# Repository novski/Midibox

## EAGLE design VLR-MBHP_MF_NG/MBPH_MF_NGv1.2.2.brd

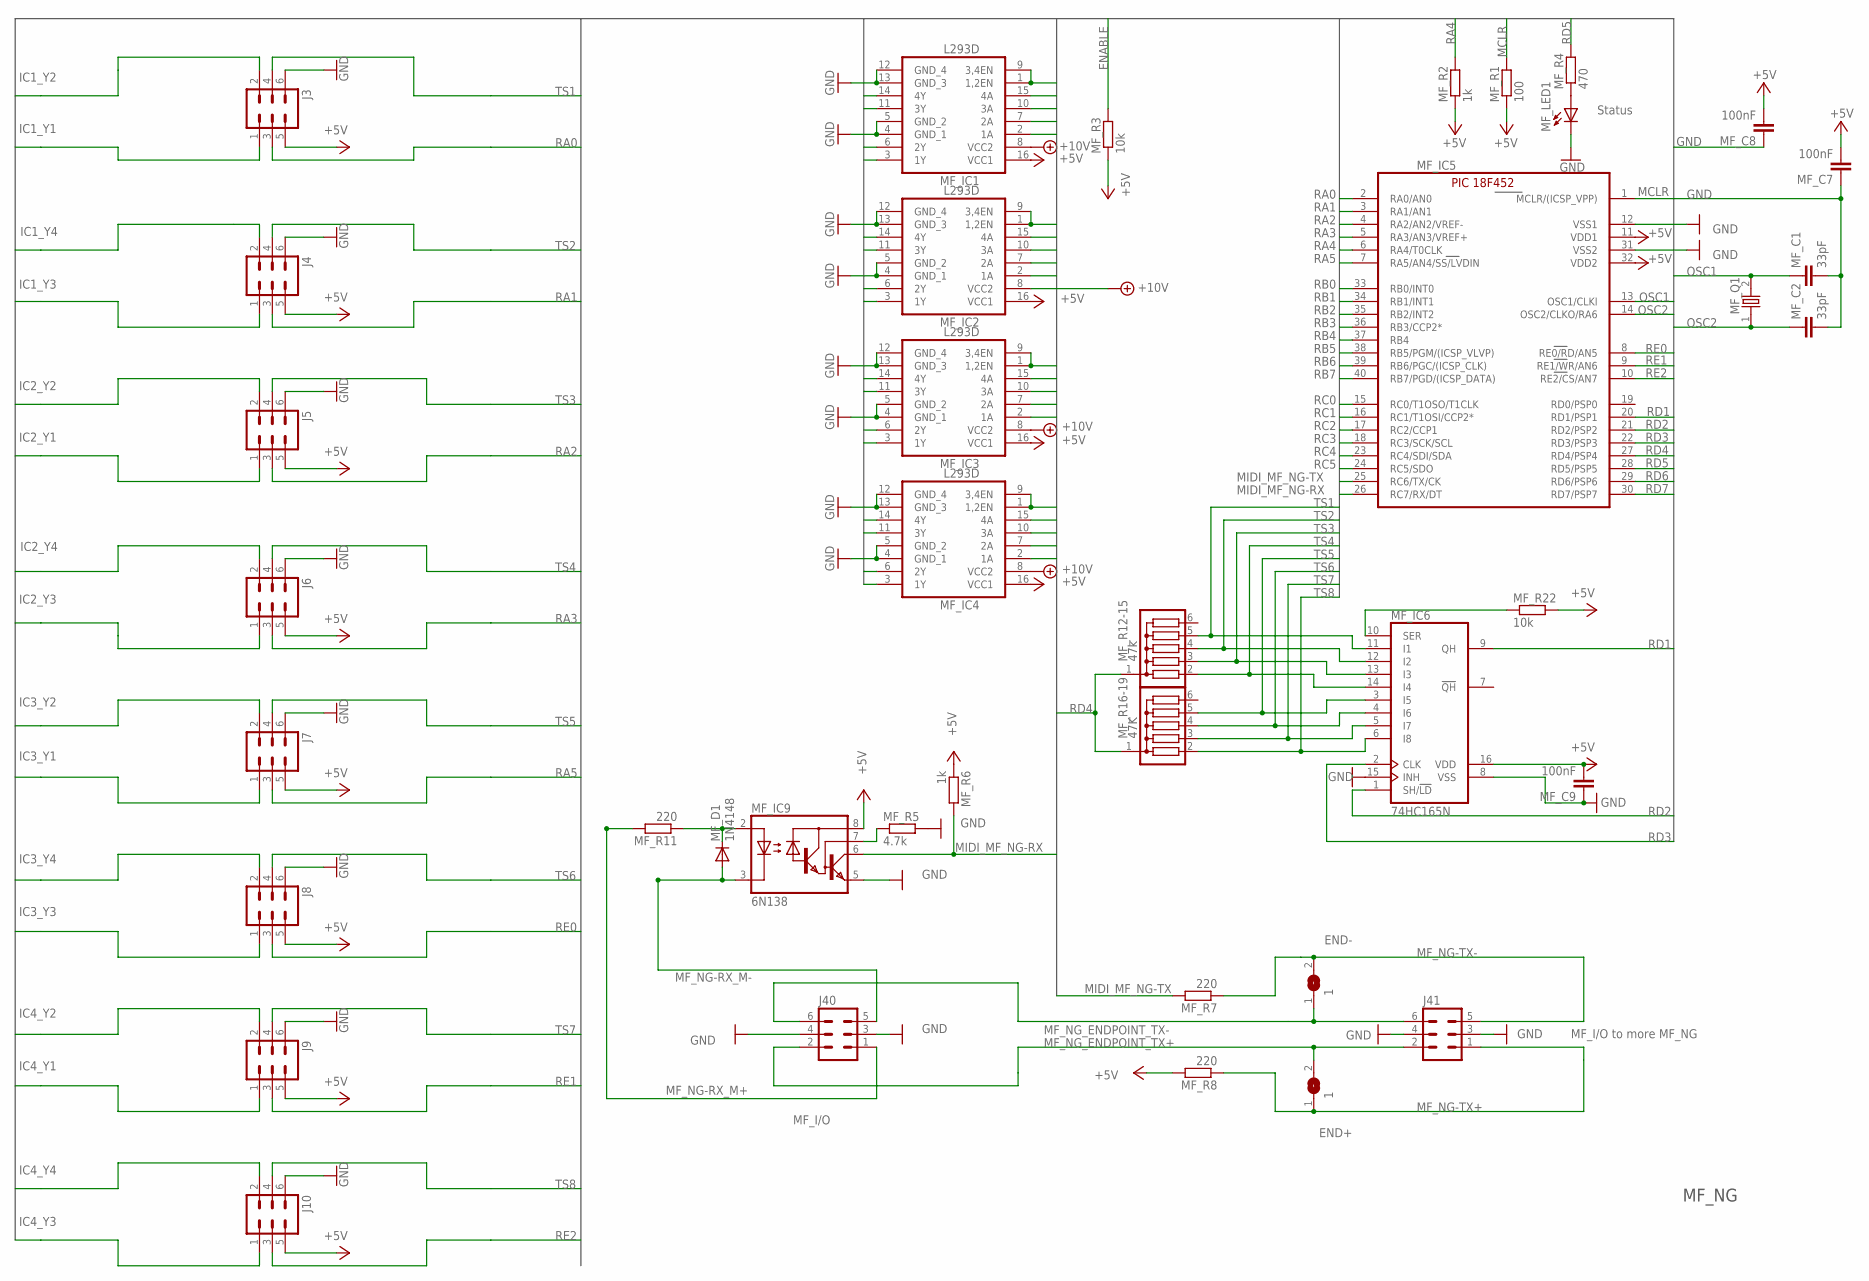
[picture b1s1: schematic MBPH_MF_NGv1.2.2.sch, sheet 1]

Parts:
END+: 1; SJ
END-: 1; SJ
J3, J4, J5, J6, J7, J8, J9, J10: ML6
J40: MF_I/O; ML6
J41: MF_I/O to more MF_NG; ML6
MF_C1, MF_C2: 33pF; C025-030X050
MF_C7, MF_C8, MF_C9: 100nF; C5B3
MF_D1: 1N4148; DO35-7
MF_IC1, MF_IC2, MF_IC3, MF_IC4: L293D; DIL16
MF_IC5: PIC18F452; DIL40
MF_IC6: 74HC165N; DIL16
MF_IC9: 6N138; DIL08
MF_LED1: Status; LED3MM
MF_Q1: ECS-100-20-4X-DU; HC-49/USX
MF_R1: 100; 0204/7
MF_R2, MF_R6: 1k; 0204/7
MF_R3, MF_R22: 10k; 0204/7
MF_R4: 470; 0204/7
MF_R5: 4.7k; 0204/7
MF_R7, MF_R8, MF_R11: 220; 0204/7
MF_R12-15: 47k; SIL6
MF_R16-19: 47K; SIL6

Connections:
+5V: J3.5, J4.5, J5.5, J6.5, J7.5, J8.5, J9.5, J10.5, MF_C7.2, MF_C8.2, MF_C9.2, MF_IC1.16 (VCC1), MF_IC2.16 (VCC1), MF_IC3.16 (VCC1), MF_IC4.16 (VCC1), MF_IC5.11 (VDD1), MF_IC5.32 (VDD2), MF_IC6.16 (VDD), MF_IC9.8 (VCC), MF_R1.1, MF_R2.1, MF_R3.1, MF_R6.1, MF_R8.2, MF_R22.2; also elsewhere on the board
+10V: MF_IC1.8 (VCC2), MF_IC2.8 (VCC2), MF_IC3.8 (VCC2), MF_IC4.8 (VCC2); also elsewhere on the board
ENABLE: MF_IC1.1 (1,2EN), MF_IC1.9 (3,4EN), MF_IC2.1 (1,2EN), MF_IC2.9 (3,4EN), MF_IC3.1 (1,2EN), MF_IC3.9 (3,4EN), MF_IC4.1 (1,2EN), MF_IC4.9 (3,4EN), MF_R3.2
GND: J3.6, J4.6, J5.6, J6.6, J7.6, J8.6, J9.6, J10.6, J40.3, J40.4, J41.3, J41.4, MF_C1.2, MF_C2.2, MF_C7.1, MF_C8.1, MF_C9.1, MF_IC1.4 (GND_1), MF_IC1.5 (GND_2), MF_IC1.12 (GND_4), MF_IC1.13 (GND_3), MF_IC2.4 (GND_1), MF_IC2.5 (GND_2), MF_IC2.12 (GND_4), MF_IC2.13 (GND_3), MF_IC3.4 (GND_1), MF_IC3.5 (GND_2), MF_IC3.12 (GND_4), MF_IC3.13 (GND_3), MF_IC4.4 (GND_1), MF_IC4.5 (GND_2), MF_IC4.12 (GND_4), MF_IC4.13 (GND_3), MF_IC5.12 (VSS1), MF_IC5.31 (VSS2), MF_IC6.8 (VSS), MF_IC6.15 (INH), MF_IC9.5 (GND), MF_LED1.K (C), MF_R5.2; also elsewhere on the board
IC1_Y1: J3.1, MF_IC1.3 (1Y)
IC1_Y2: J3.2, MF_IC1.6 (2Y)
IC1_Y3: J4.1, MF_IC1.11 (3Y)
IC1_Y4: J4.2, MF_IC1.14 (4Y)
IC2_Y1: J5.1, MF_IC2.3 (1Y)
IC2_Y2: J5.2, MF_IC2.6 (2Y)
IC2_Y3: J6.1, MF_IC2.11 (3Y)
IC2_Y4: J6.2, MF_IC2.14 (4Y)
IC3_Y1: J7.1, MF_IC3.3 (1Y)
IC3_Y2: J7.2, MF_IC3.6 (2Y)
IC3_Y3: J8.1, MF_IC3.11 (3Y)
IC3_Y4: J8.2, MF_IC3.14 (4Y)
IC4_Y1: J9.1, MF_IC4.3 (1Y)
IC4_Y2: J9.2, MF_IC4.6 (2Y)
IC4_Y3: J10.1, MF_IC4.11 (3Y)
IC4_Y4: J10.2, MF_IC4.14 (4Y)
MCLR: MF_IC5.1 (MCLR/(ICSP_VPP)), MF_R1.2
MF_NG-RX_M+: J40.1, MF_R11.2
MF_NG-RX_M-: J40.5, MF_D1.A, MF_IC9.3 (C)
MF_NG-TX+: END+.1, J41.1, MF_R8.1
MF_NG-TX-: END-.2, J41.5, MF_R7.1
MF_NG_ENDPOINT_TX+: END+.2, J40.2, J41.2
MF_NG_ENDPOINT_TX-: END-.1, J40.6, J41.6
MIDI_MF_NG-RX: MF_IC5.26 (RC7/RX/DT), MF_IC9.6 (VO), MF_R6.2
MIDI_MF_NG-TX: MF_IC5.25 (RC6/TX/CK), MF_R7.2
unnamed: MF_IC6.10 (SER), MF_R22.1
unnamed: MF_LED1.A, MF_R4.1
unnamed: MF_IC9.7 (VB), MF_R5.1
unnamed: MF_D1.C, MF_IC9.2 (A), MF_R11.1
OSC1: MF_C1.1, MF_IC5.13 (OSC1/CLKI), MF_Q1.2
OSC2: MF_C2.1, MF_IC5.14 (OSC2/CLKO/RA6), MF_Q1.1
RA0: J3.3, MF_IC5.2 (RA0/AN0)
RA1: J4.3, MF_IC5.3 (RA1/AN1)
RA2: J5.3, MF_IC5.4 (RA2/AN2/VREF-)
RA3: J6.3, MF_IC5.5 (RA3/AN3/VREF+)
RA4: MF_IC5.6 (RA4/T0CLK), MF_R2.2
RA5: J7.3, MF_IC5.7 (RA5/AN4/SS/LVDIN)
RB0: MF_IC2.15 (4A), MF_IC5.33 (RB0/INT0)
RB1: MF_IC2.10 (3A), MF_IC5.34 (RB1/INT1)
RB2: MF_IC2.7 (2A), MF_IC5.35 (RB2/INT2)
RB3: MF_IC2.2 (1A), MF_IC5.36 (RB3/CCP2*)
RB4: MF_IC1.15 (4A), MF_IC5.37 (RB4)
RB5: MF_IC1.10 (3A), MF_IC5.38 (RB5/PGM/(ICSP_VLVP))
RB6: MF_IC1.7 (2A), MF_IC5.39 (RB6/PGC/(ICSP_CLK))
RB7: MF_IC1.2 (1A), MF_IC5.40 (RB7/PGD/(ICSP_DATA))
RC0: MF_IC4.15 (4A), MF_IC5.15 (RC0/T1OSO/T1CLK)
RC1: MF_IC4.10 (3A), MF_IC5.16 (RC1/T1OSI/CCP2*)
RC2: MF_IC4.7 (2A), MF_IC5.17 (RC2/CCP1)
RC3: MF_IC4.2 (1A), MF_IC5.18 (RC3/SCK/SCL)
RC4: MF_IC3.15 (4A), MF_IC5.23 (RC4/SDI/SDA)
RC5: MF_IC3.10 (3A), MF_IC5.24 (RC5/SDO)
RD1: MF_IC5.20 (RD1/PSP1), MF_IC6.9 (QH)
RD2: MF_IC5.21 (RD2/PSP2), MF_IC6.1 (SH/!LD)
RD3: MF_IC5.22 (RD3/PSP3), MF_IC6.2 (CLK)
RD4: MF_IC5.27 (RD4/PSP4), MF_R12-15.1, MF_R16-19.1
RD5: MF_IC5.28 (RD5/PSP5), MF_R4.2
RD6: MF_IC3.7 (2A), MF_IC5.29 (RD6/PSP6)
RD7: MF_IC3.2 (1A), MF_IC5.30 (RD7/PSP7)
RE0: J8.3, MF_IC5.8 (RE0/RD/AN5)
RE1: J9.3, MF_IC5.9 (RE1/WR/AN6)
RE2: J10.3, MF_IC5.10 (RE2/CS/AN7)
TS1: J3.4, MF_IC6.11 (I1), MF_R12-15.5
TS2: J4.4, MF_IC6.12 (I2), MF_R12-15.4
TS3: J5.4, MF_IC6.13 (I3), MF_R12-15.3
TS4: J6.4, MF_IC6.14 (I4), MF_R12-15.2
TS5: J7.4, MF_IC6.3 (I5), MF_R16-19.5
TS6: J8.4, MF_IC6.4 (I6), MF_R16-19.4
TS7: J9.4, MF_IC6.5 (I7), MF_R16-19.3
TS8: J10.4, MF_IC6.6 (I8), MF_R16-19.2

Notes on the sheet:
MF_NG

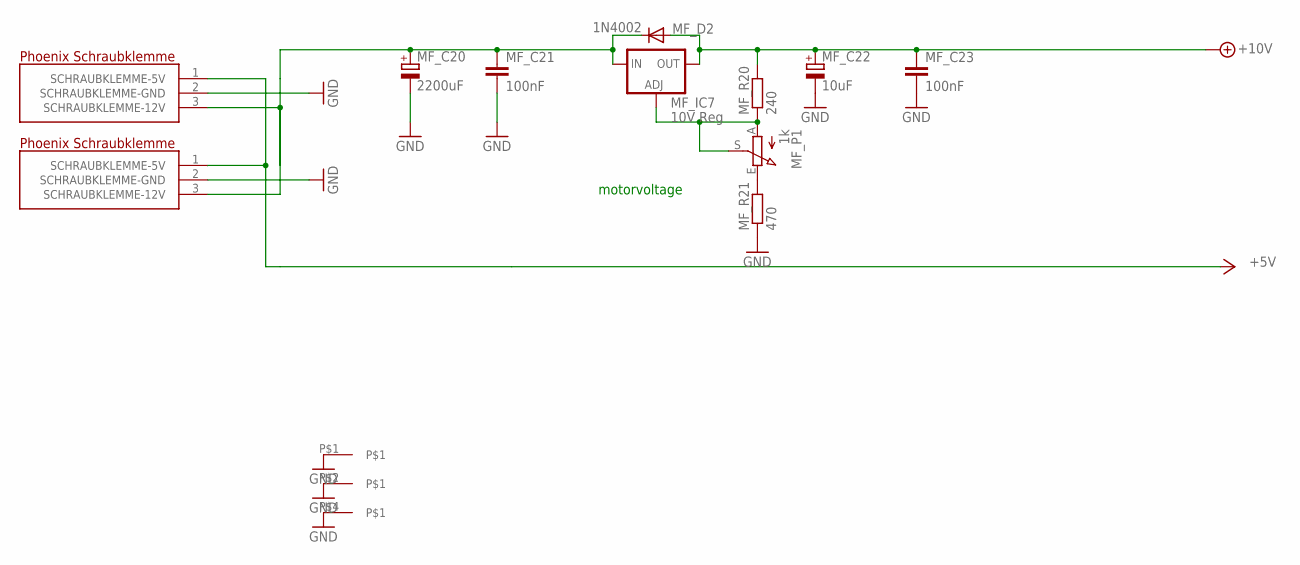
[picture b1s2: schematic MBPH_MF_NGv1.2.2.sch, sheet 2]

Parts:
KLEMME1, KLEMME2: PT-1.5/3; PT-1.5/3-5.0
MF_C20: 2200uF; E5-13
MF_C21, MF_C23: 100nF; C5B3
MF_C22: 10uF; E2,5-6E
MF_D2: 1N4002; D040-10
MF_IC7: 10V Reg; 317TS
MF_P1: 1k; 6MM_V
MF_R20: 240; 0204/7
MF_R21: 470; 0204/7
U$3: MIDIBOX_HALF; MIDIBOX14X6

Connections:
+5V: KLEMME1.1 (SCHRAUBKLEMME-5V), KLEMME2.1 (SCHRAUBKLEMME-5V); also elsewhere on the board
+10V: MF_C22.+, MF_C23.1, MF_D2.A, MF_IC7.2 (OUT), MF_R20.2; also elsewhere on the board
+12V: KLEMME1.3 (SCHRAUBKLEMME-12V), KLEMME2.3 (SCHRAUBKLEMME-12V), MF_C20.+, MF_C21.1, MF_D2.C, MF_IC7.3 (IN)
GND: KLEMME1.2 (SCHRAUBKLEMME-GND), KLEMME2.2 (SCHRAUBKLEMME-GND), MF_C20.-, MF_C21.2, MF_C22.-, MF_C23.2, MF_R21.1, U$3.P$1, U$3.P$2, U$3.P$4; also elsewhere on the board
unnamed: MF_IC7.1 (ADJ), MF_P1.A, MF_P1.S, MF_R20.1
unnamed: MF_P1.E, MF_R21.2

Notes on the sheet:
motorvoltage

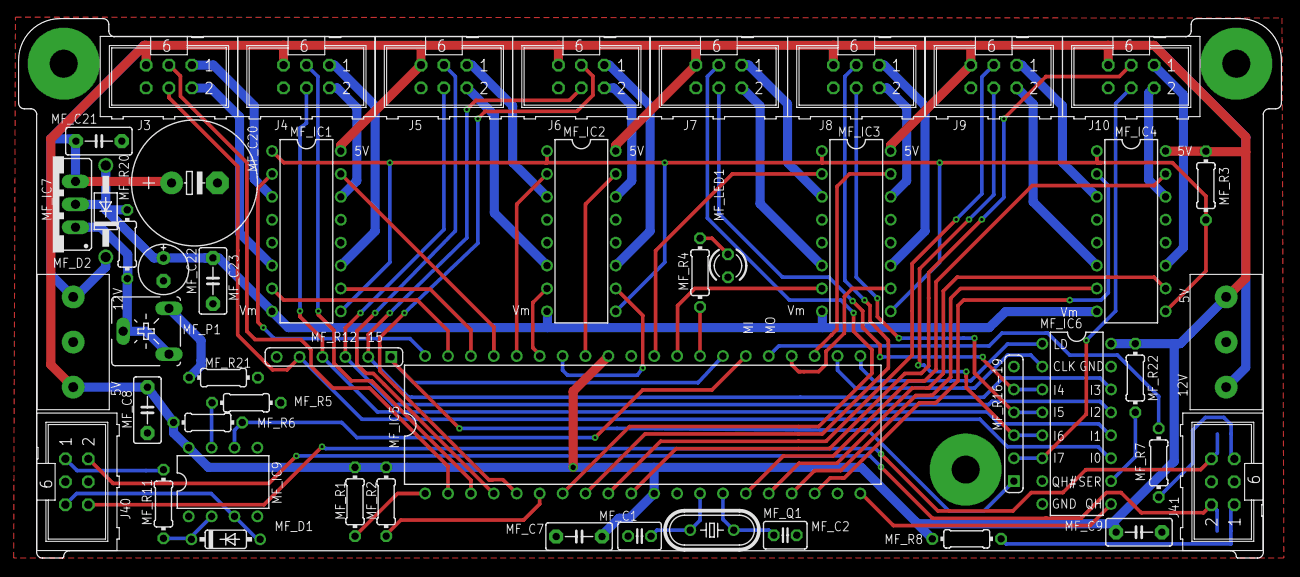
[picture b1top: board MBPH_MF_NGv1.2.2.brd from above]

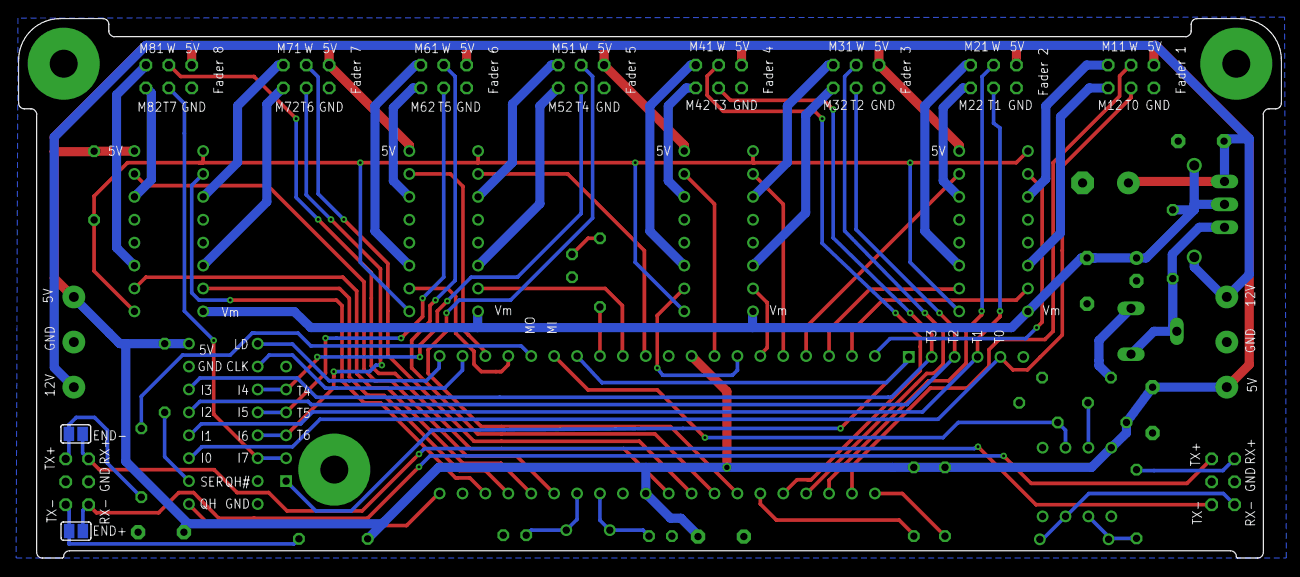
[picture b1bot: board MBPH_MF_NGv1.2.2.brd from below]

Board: 2 copper layers, 140.0 x 59.8 mm, 51 parts (2 on the bottom side), 76 nets.

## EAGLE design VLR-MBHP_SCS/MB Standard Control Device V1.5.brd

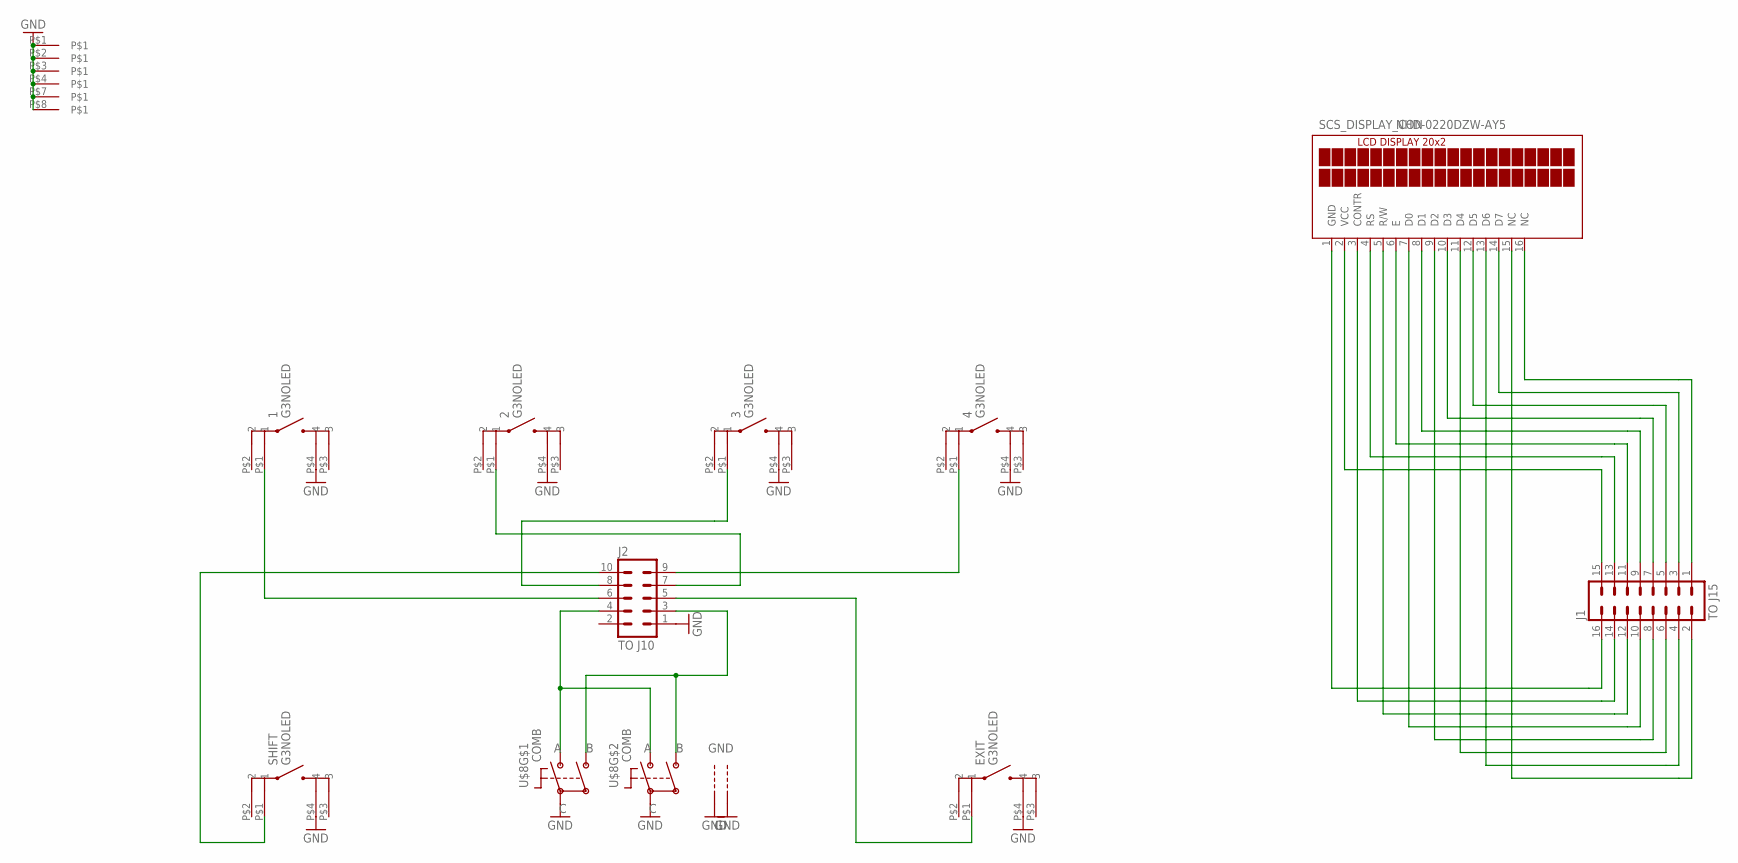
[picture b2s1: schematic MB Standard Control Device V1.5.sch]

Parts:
1, 2, 3, 4: G3NOLED
EXIT: G3NOLED
J1: TO J15; ML16
J2: TO J10; ML10
SCS_DISPLAY_CON: NHD-0220DZW-AY5
SHIFT: G3NOLED
U$2: MIDIBOX_FULL; MIDIBOX14X12
U$8: COMB; COMB_PEC11&STEC16

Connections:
GND: 1.P$4 (4), 2.P$4 (4), 3.P$4 (4), 4.P$4 (4), EXIT.P$4 (4), J2.1, SHIFT.P$4 (4), U$2.P$1, U$2.P$2, U$2.P$3, U$2.P$4, U$2.P$7, U$2.P$8, U$8.P$C, U$8.P$C1 (P$C), U$8.P$GND1, U$8.P$GND2
unnamed: J1.16, SCS_DISPLAY_CON.1 (GND)
unnamed: J1.15, SCS_DISPLAY_CON.2 (VCC)
unnamed: J1.14, SCS_DISPLAY_CON.3 (CONTR)
unnamed: J1.13, SCS_DISPLAY_CON.4 (RS)
unnamed: J1.12, SCS_DISPLAY_CON.5 (R/W)
unnamed: J1.11, SCS_DISPLAY_CON.6 (E)
unnamed: J1.10, SCS_DISPLAY_CON.7 (D0)
unnamed: J1.9, SCS_DISPLAY_CON.8 (D1)
unnamed: J1.8, SCS_DISPLAY_CON.9 (D2)
unnamed: J1.7, SCS_DISPLAY_CON.10 (D3)
unnamed: J1.6, SCS_DISPLAY_CON.11 (D4)
unnamed: J1.5, SCS_DISPLAY_CON.12 (D5)
unnamed: J1.4, SCS_DISPLAY_CON.13 (D6)
unnamed: J1.3, SCS_DISPLAY_CON.14 (D7)
unnamed: J1.2, SCS_DISPLAY_CON.15 (NC)
unnamed: J1.1, SCS_DISPLAY_CON.16 (NC)
unnamed: 1.P$1 (1), J2.6
unnamed: J2.10, SHIFT.P$1 (1)
unnamed: 2.P$1 (1), J2.7
unnamed: 3.P$1 (1), J2.8
unnamed: 4.P$1 (1), J2.9
unnamed: EXIT.P$1 (1), J2.5
unnamed: J2.4, U$8.P$A, U$8.P$A1 (P$A)
unnamed: J2.3, U$8.P$B, U$8.P$B1 (P$B)

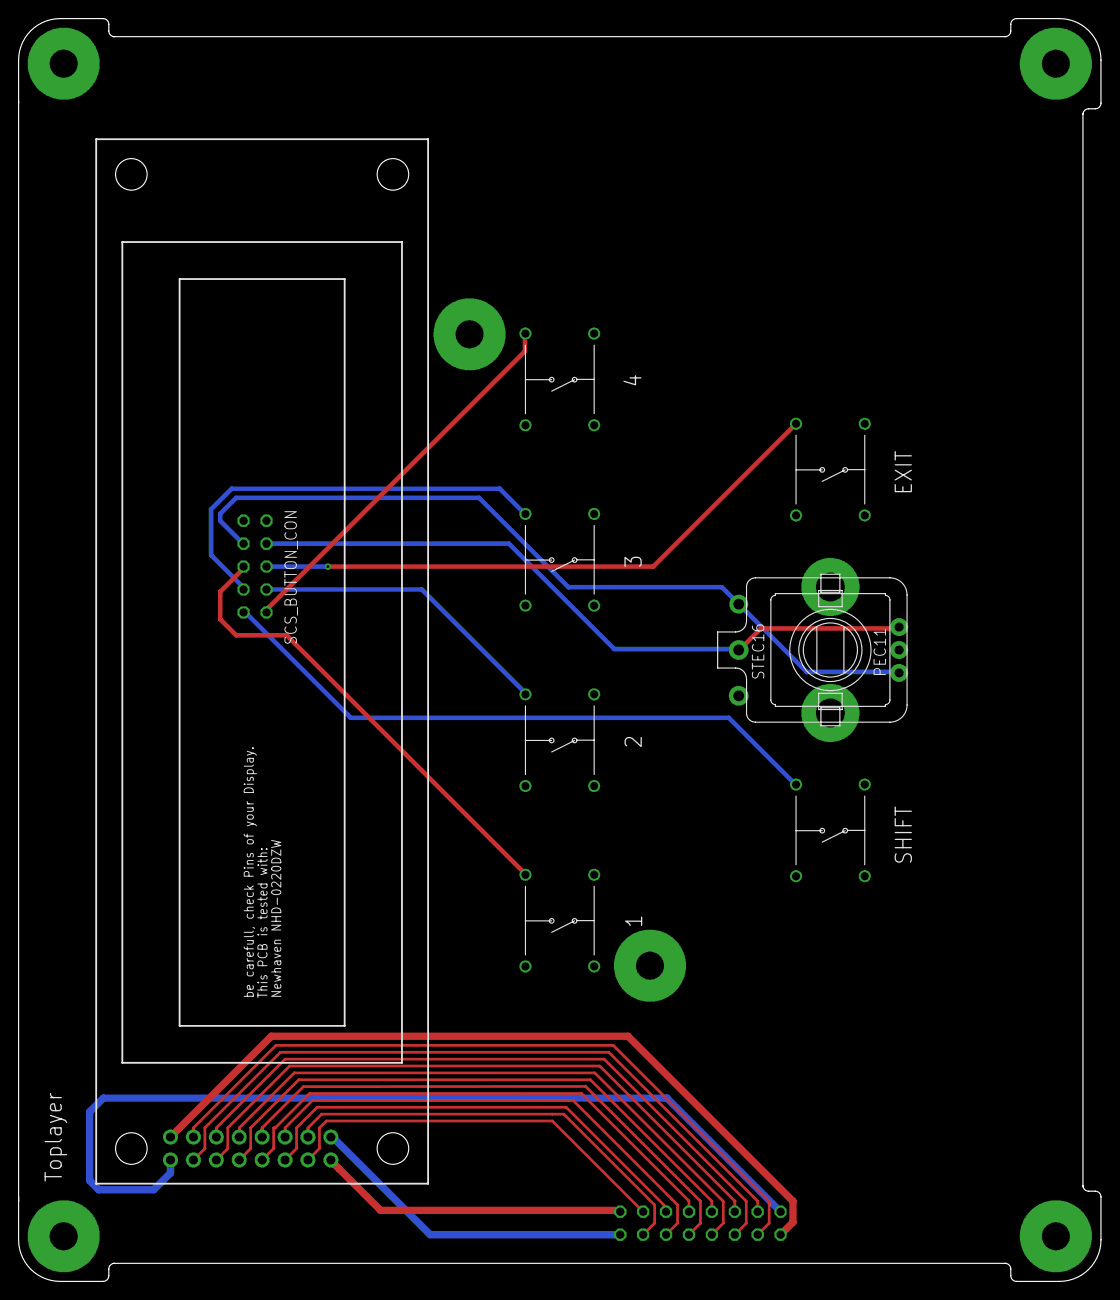
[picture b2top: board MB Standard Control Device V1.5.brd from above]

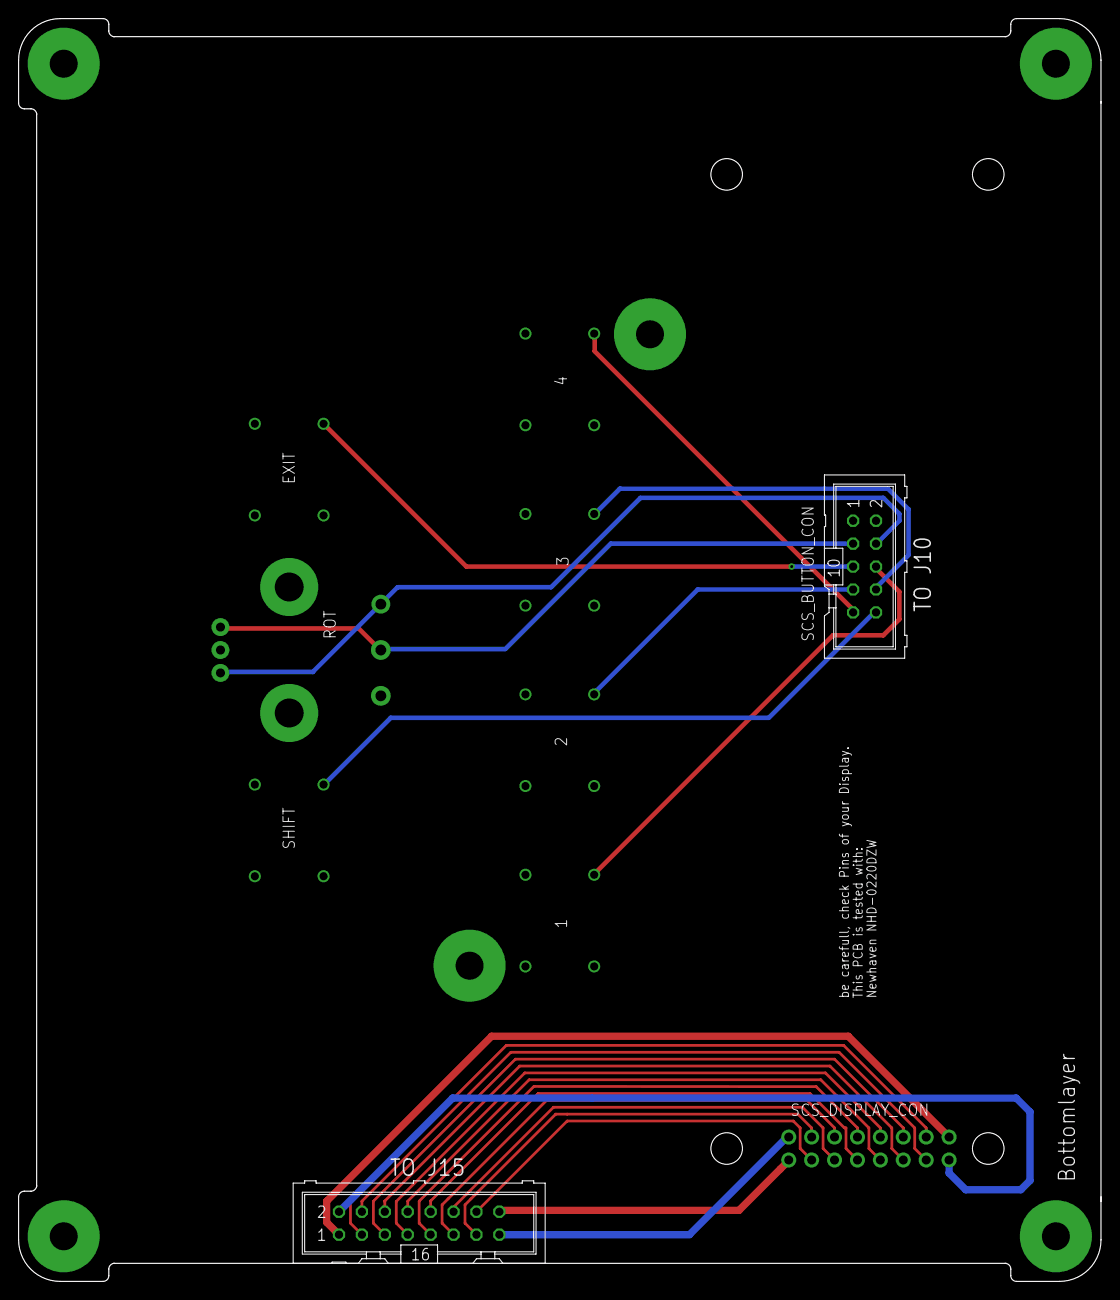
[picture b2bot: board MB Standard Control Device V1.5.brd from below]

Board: 2 copper layers, 120.0 x 140.0 mm, 17 parts (5 on the bottom side), 25 nets.

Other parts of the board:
U$3, U$5: (C)T.KLOSE
U$4, U$12: SCS
U$6, U$11: VLRLAB

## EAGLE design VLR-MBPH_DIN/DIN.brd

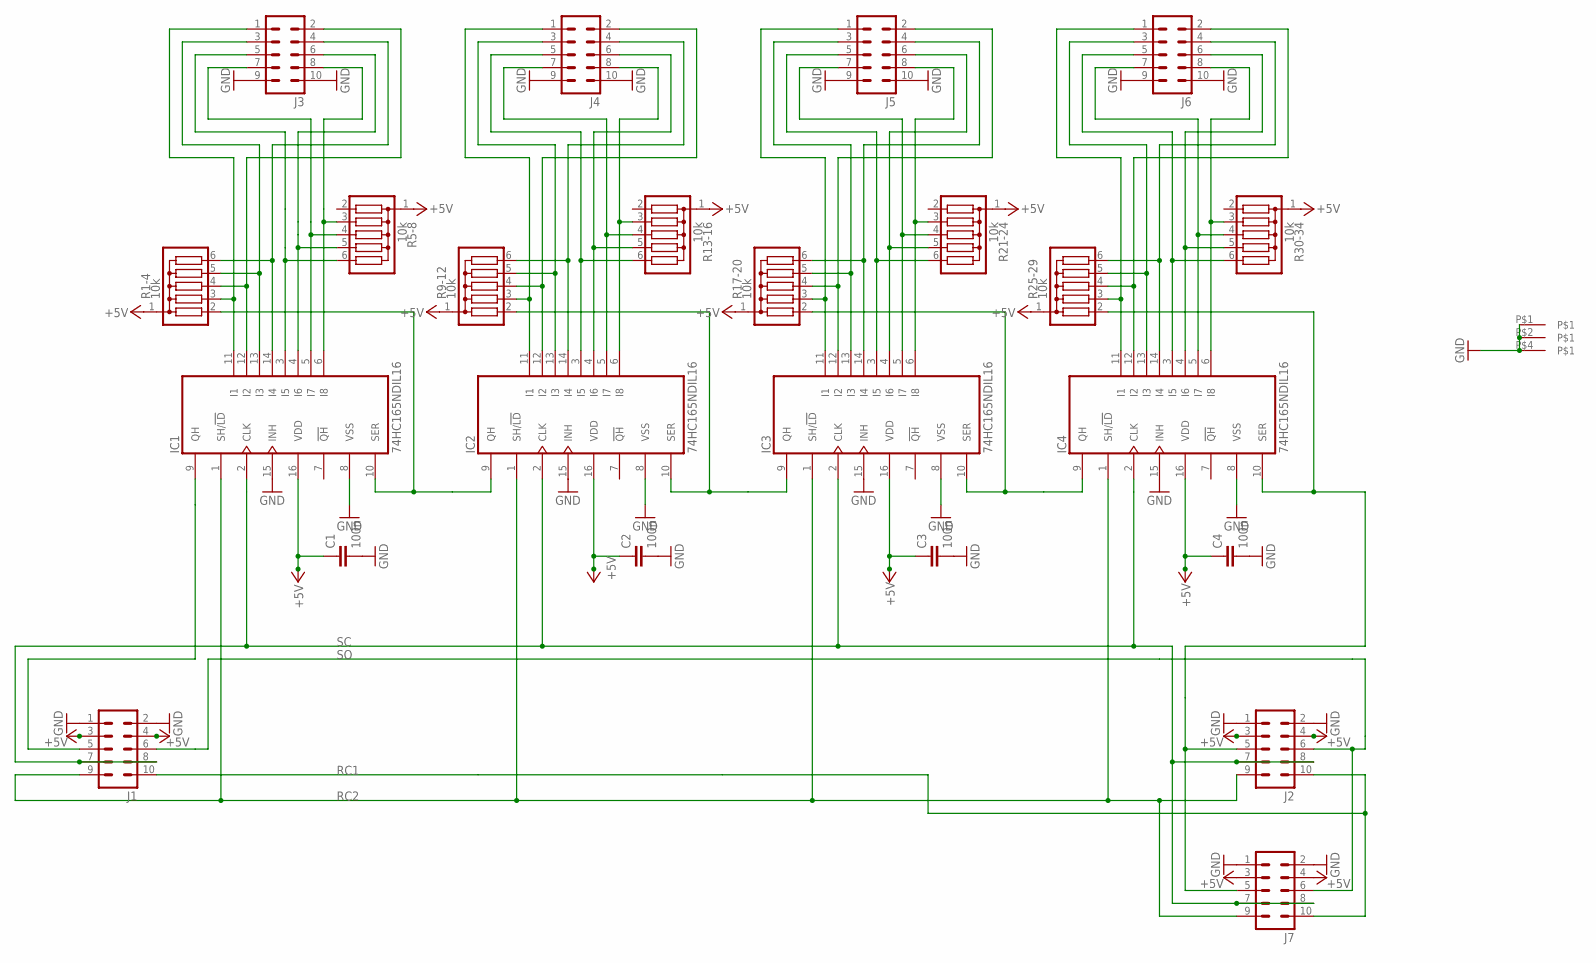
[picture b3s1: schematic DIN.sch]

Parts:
C1, C2, C3, C4: 100n; C025-025X050
IC1, IC2, IC3, IC4: 74HC165NDIL16; DIL16
J1, J2, J3, J4, J5, J6, J7: ML10
R1-4, R5-8, R9-12, R13-16, R17-20, R21-24, R25-29, R30-34: 10k; SIL6
U$7: MIDIBOX_HALF; MIDIBOX14X6

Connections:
+5V: C1.1, C2.1, C3.1, C4.1, IC1.16 (VDD), IC2.16 (VDD), IC3.16 (VDD), IC4.16 (VDD), J1.3, J1.4, J2.3, J2.4, J7.3, J7.4, R1-4.1, R5-8.1, R9-12.1, R13-16.1, R17-20.1, R21-24.1, R25-29.1, R30-34.1
GND: C1.2, C2.2, C3.2, C4.2, IC1.8 (VSS), IC1.15 (INH), IC2.8 (VSS), IC2.15 (INH), IC3.8 (VSS), IC3.15 (INH), IC4.8 (VSS), IC4.15 (INH), J1.1, J1.2, J2.1, J2.2, J3.9, J3.10, J4.9, J4.10, J5.9, J5.10, J6.9, J6.10, J7.1, J7.2, U$7.P$1, U$7.P$2, U$7.P$4
unnamed: IC1.11 (I1), J3.1, R1-4.3
unnamed: IC1.12 (I2), J3.2, R1-4.4
unnamed: IC1.13 (I3), J3.3, R1-4.5
unnamed: IC1.14 (I4), J3.4, R1-4.6
unnamed: IC1.3 (I5), J3.5, R5-8.6
unnamed: IC1.4 (I6), J3.6, R5-8.5
unnamed: IC1.5 (I7), J3.7, R5-8.4
unnamed: IC1.6 (I8), J3.8, R5-8.3
unnamed: IC2.11 (I1), J4.1, R9-12.3
unnamed: IC2.12 (I2), J4.2, R9-12.4
unnamed: IC2.13 (I3), J4.3, R9-12.5
unnamed: IC2.14 (I4), J4.4, R9-12.6
unnamed: IC2.3 (I5), J4.5, R13-16.6
unnamed: IC2.4 (I6), J4.6, R13-16.5
unnamed: IC2.5 (I7), J4.7, R13-16.4
unnamed: IC2.6 (I8), J4.8, R13-16.3
unnamed: IC3.11 (I1), J5.1, R17-20.3
unnamed: IC3.12 (I2), J5.2, R17-20.4
unnamed: IC3.13 (I3), J5.3, R17-20.5
unnamed: IC3.14 (I4), J5.4, R17-20.6
unnamed: IC3.3 (I5), J5.5, R21-24.6
unnamed: IC3.4 (I6), J5.6, R21-24.5
unnamed: IC3.5 (I7), J5.7, R21-24.4
unnamed: IC3.6 (I8), J5.8, R21-24.3
unnamed: IC4.11 (I1), J6.1, R25-29.3
unnamed: IC4.12 (I2), J6.2, R25-29.4
unnamed: IC4.13 (I3), J6.3, R25-29.5
unnamed: IC4.14 (I4), J6.4, R25-29.6
unnamed: IC4.3 (I5), J6.5, R30-34.6
unnamed: IC4.4 (I6), J6.6, R30-34.5
unnamed: IC4.5 (I7), J6.7, R30-34.4
unnamed: IC4.6 (I8), J6.8, R30-34.3
unnamed: IC1.10 (SER), IC2.9 (QH), R1-4.2
unnamed: IC2.10 (SER), IC3.9 (QH), R9-12.2
unnamed: IC3.10 (SER), IC4.9 (QH), R17-20.2
RC1: J1.10, J2.10, J7.10
RC2: IC1.1 (SH/!LD), IC2.1 (SH/!LD), IC3.1 (SH/!LD), IC4.1 (SH/!LD), J1.9, J2.9, J7.9
SC: IC1.2 (CLK), IC2.2 (CLK), IC3.2 (CLK), IC4.2 (CLK), J1.7, J1.8, J2.7, J2.8, J7.7, J7.8
SI: IC1.9 (QH), J1.5
SI2: IC4.10 (SER), J2.5, J7.5, R25-29.2
SO: J1.6, J2.6, J7.6

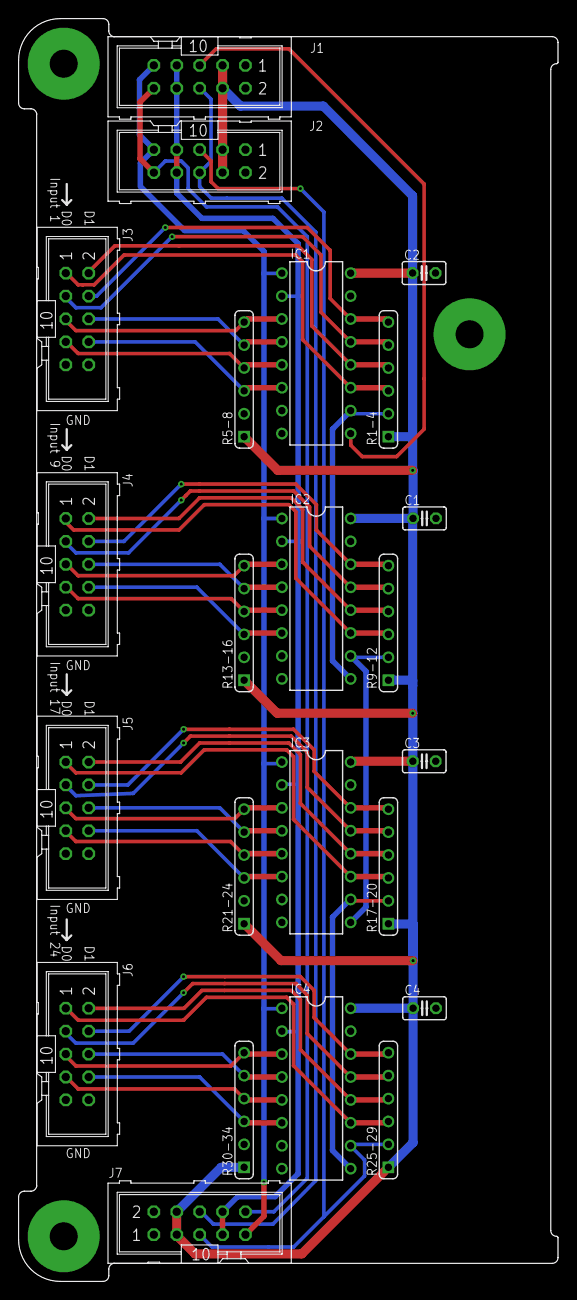
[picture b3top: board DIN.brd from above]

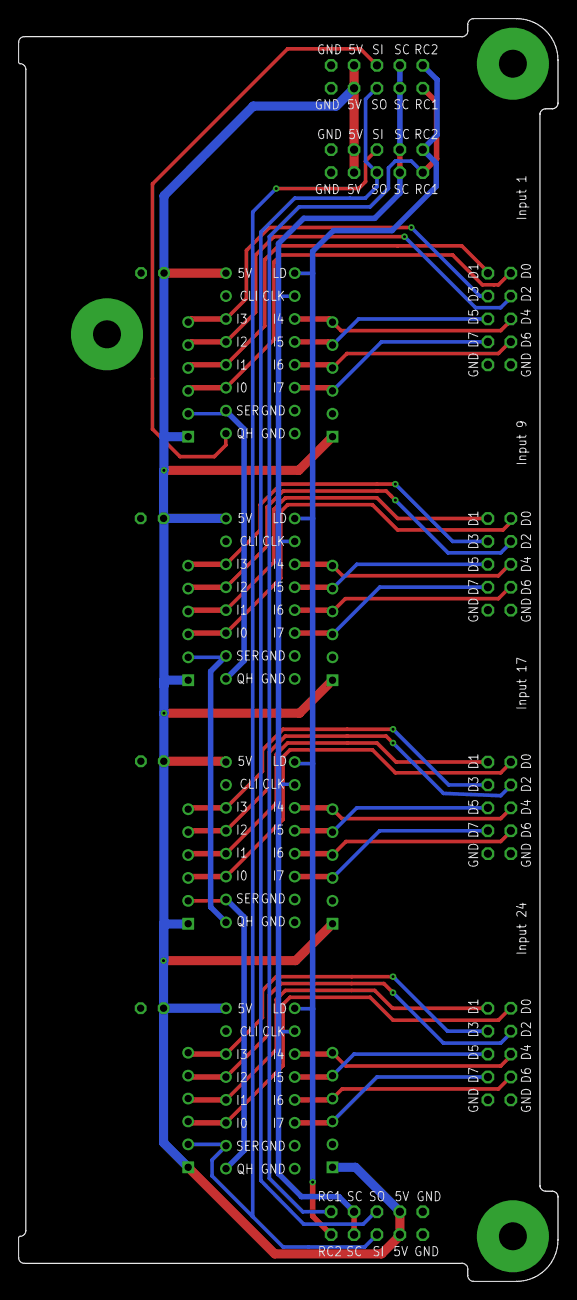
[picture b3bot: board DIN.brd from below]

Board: 2 copper layers, 59.8 x 140.0 mm, 28 parts (2 on the bottom side), 43 nets.

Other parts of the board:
U$3, U$4: VLRLAB
U$5, U$6: DIN

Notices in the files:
parts and their libraries:
Frames_VLR: © VLRlab Hörler
